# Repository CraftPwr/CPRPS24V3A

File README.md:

# **Craft Power Labs - Open Source Lab Equipment Initiative**  
### **Bench Top Power Supply - CPRPS24V3A**  
An open-source variable lab bench power supply designed for education, hobbyists, and non-profit initiatives. Part of the **Craft Power Labs Initiative**, funded initially by **DERBI / Nidhi Prayas**.  

---

## **📜 Project Overview**  
Craft Power Labs aims to provide accessible, high-quality, and open-source lab equipment for electronics learning and research. This power supply is built to match the essential features of commercial-grade bench power supplies while remaining completely open-source for personal, educational, and non-commercial use.  

---

## **📊 Technical Specifications (Datasheet)**  

| **Feature**             | **Specification**             |
|-------------------------|-----------------------------|
| **Input Supply**        | 110V ~ 220V AC              |
| **Variable Voltage**    | 0V to 24V                   |
| **Current Capacity**    | Up to 3A                    |
| **Voltage Resolution**  | 10mV                        |
| **Current Limit Resolution** | 50mA                 |
| **Voltmeter Resolution** | 100mV                      |
| **Ammeter Resolution**  | 100mA                        |
| **Noise & Ripple (@ 20MHz)** | < 50mV               |
| **Operating Modes**     | Constant Voltage (CV), Constant Current (CC) |
| **Safety Features**     | Over Current, Short Circuit, Reverse Voltage Bypass |
| **Display**            | 1-inch Volt-Amp Meter Digits |
| **Control**            | Multi-Turn Potentiometers    |
| **Connectors**         | 4mm Banana Sockets          |
| **AC Port**            | IEC 14 Port with Illuminated SPST Switch + Fuse |

---

## **📷 Images & Renders**  

---

## **📜 Licensing**  
This project is licensed under **CC BY-NC-SA 4.0**, which means:  
✔ Free to use, modify, and distribute for personal, educational, and non-commercial purposes.  
✔ Must provide attribution and share derivative works under the same license.  
❌ **Not for commercial use** without explicit permission.  

For more details, see: [LICENSE.md](./LICENSE.md)  

📩 **For inquiries, contact us:**  
**Email:** [connect@craftpower.cc](mailto:connect@craftpower.cc)  
**Website:** [https://craftpower.cc](https://craftpower.cc)  

---

## **🛠 Getting Started**  
### **1️⃣ Hardware Design**  
- Schematic and PCB files are available in the `/hardware` directory.  
- Designed using **KiCad**.  

### **2️⃣ Assembly & Testing**  
- Refer to the `assembly_guide.md` for step-by-step assembly instructions.  
- Use the `calibration_guide.md` to fine-tune voltage and current accuracy.  

---

## **🛠 Contributing**  
We welcome contributions! If you'd like to improve the design, add new features, or fix bugs:  
1. Fork this repository  
2. Create a new branch (`feature-new-component`)  
3. Submit a Pull Request  

---

## **🌍 Join the Community**  
Be part of our mission to make electronics lab equipment open-source and accessible.  

💬 **Join our discussion forum**: [Forum Link]  
📢 **Follow updates**: [Social Media Link]  

---

🚀 **Craft Power Labs - Powering Learning, One Bench at a Time!**

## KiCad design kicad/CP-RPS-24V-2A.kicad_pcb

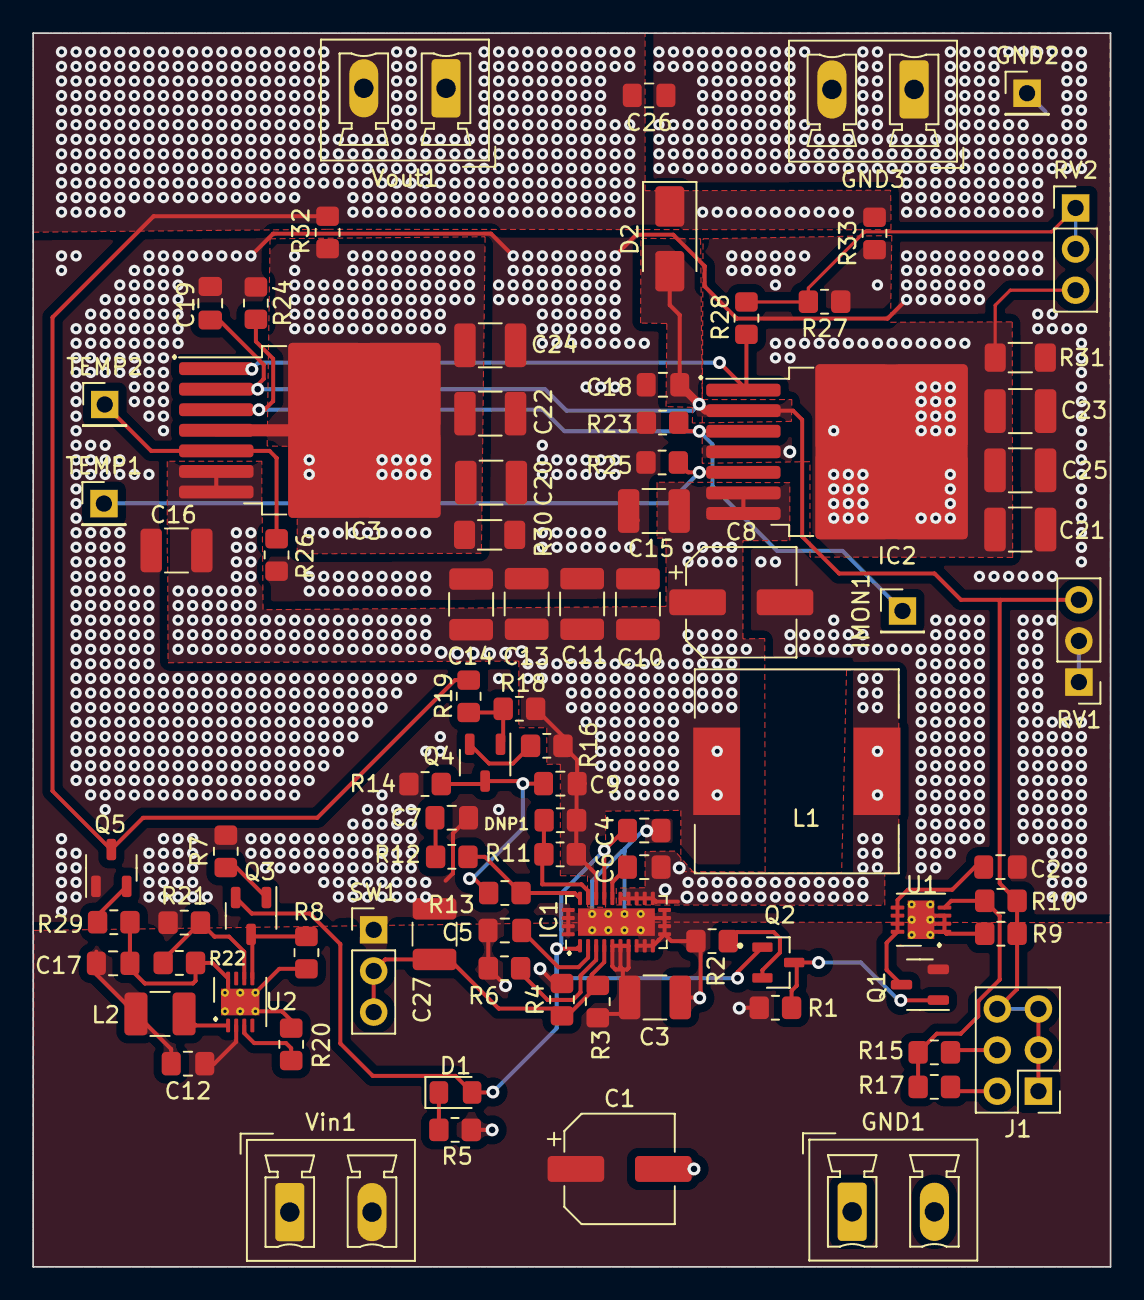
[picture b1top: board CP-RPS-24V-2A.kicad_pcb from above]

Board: 2 copper layers, 66.5 x 76.2 mm, 87 parts (0 on the bottom side), 39 nets.

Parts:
C1: 22uF; CP_Elec_6.3x7.7
C2, C4, C12, C26: 1uF; C_0805_2012Metric_Pad1.18x1.45mm_HandSolder
C3: 10uF 50V; C_1210_3225Metric_Pad1.33x2.70mm_HandSolder
C5, C6: 0.1uF; C_0805_2012Metric_Pad1.18x1.45mm_HandSolder
C7: (OPT); C_0805_2012Metric_Pad1.18x1.45mm_HandSolder
C8: 100uF; CP_Elec_6.3x7.7
C9: 1nF; C_0805_2012Metric_Pad1.18x1.45mm_HandSolder
C10: DNP; C_1210_3225Metric_Pad1.33x2.70mm_HandSolder
C11, C13, C14, C15, C16, C20, C21, C22, C23, C24, C25: 10uF; C_1210_3225Metric_Pad1.33x2.70mm_HandSolder
C17: 10uF; C_0805_2012Metric_Pad1.18x1.45mm_HandSolder
C18, C19: 0.01uF; C_0805_2012Metric_Pad1.18x1.45mm_HandSolder
C27: 39.6uF; C_1210_3225Metric_Pad1.33x2.70mm_HandSolder
D1: LED; LED_0805_2012Metric_Pad1.15x1.40mm_HandSolder
D2: B140; D_SMA
DNP1: 5.1K; R_0805_2012Metric_Pad1.20x1.40mm_HandSolder
GND1, GND3: PhoenixContact_MCV_1,5_2-G-5.08_1x02_P5.08mm_Vertical
GND2: TestPoint; PinHeader_1x01_P2.54mm_Vertical
IC1: LT8612EUDE#PBF; QFN-28-1EP_3x6mm_P0.5mm_EP1.7x4.75mm_ThermalVias
IC2, IC3: LT3081ER_PBF; TO-263-7_TabPin8
IMON1: 10V-40V; PinHeader_1x01_P2.54mm_Vertical
J1: Conn_02x03_Odd_Even; PinHeader_2x03_P2.54mm_Vertical
L1: 5.5uH; L_12x12mm_H4.5mm
L2: 470uH; L_1210_3225Metric_Pad1.42x2.65mm_HandSolder
Q1: SI2309CDS; SOT-23-3
Q2: CMST3904; SOT95P230X110-3N
Q3, Q4: MMBT3906; SOT-23-3
Q5: FMMT493; SOT-23-3
R1, R11: 5.1K; R_0805_2012Metric_Pad1.20x1.40mm_HandSolder
R2: 2.7K; R_0805_2012Metric_Pad1.20x1.40mm_HandSolder
R3: 499K; R_0805_2012Metric_Pad1.20x1.40mm_HandSolder
R4: 54.9K; R_0805_2012Metric_Pad1.20x1.40mm_HandSolder
R5, R29: 549E; R_0805_2012Metric_Pad1.20x1.40mm_HandSolder
R6: 60.4K; R_0805_2012Metric_Pad1.20x1.40mm_HandSolder
R7: 1K; R_0805_2012Metric_Pad1.20x1.40mm_HandSolder
R8, R25, R26: 10K; R_0805_2012Metric_Pad1.20x1.40mm_HandSolder
R9: 200E; R_0805_2012Metric_Pad1.20x1.40mm_HandSolder
R10: 47.5K; R_0805_2012Metric_Pad1.20x1.40mm_HandSolder
R12: (OPT); R_0805_2012Metric_Pad1.20x1.40mm_HandSolder
R13, R16, R23, R24: 1.00K; R_0805_2012Metric_Pad1.20x1.40mm_HandSolder
R14: 4.99K; R_0805_2012Metric_Pad1.20x1.40mm_HandSolder
R15: 73.2K; R_0805_2012Metric_Pad1.20x1.40mm_HandSolder
R17: 11.3K; R_0805_2012Metric_Pad1.20x1.40mm_HandSolder
R18, R19: 100K; R_0805_2012Metric_Pad1.20x1.40mm_HandSolder
R20: 806K; R_0805_2012Metric_Pad1.20x1.40mm_HandSolder
R21: 1.47M; R_0805_2012Metric_Pad1.20x1.40mm_HandSolder
R22: 280K; R_0805_2012Metric_Pad1.20x1.40mm_HandSolder
R27: 3.92K; R_0805_2012Metric_Pad1.20x1.40mm_HandSolder
R28: 100E; R_0805_2012Metric_Pad1.20x1.40mm_HandSolder
R30, R31: 10K; R_1206_3216Metric_Pad1.30x1.75mm_HandSolder
R32, R33: 0.01E; R_0805_2012Metric_Pad1.20x1.40mm_HandSolder
RV1: 10K; PinHeader_1x03_P2.54mm_Vertical
RV2: 5K; PinHeader_1x03_P2.54mm_Vertical
SW1: SW_SPDT_321; PinHeader_1x03_P2.54mm_Vertical
TEMP1: TestPoint; PinHeader_1x01_P2.54mm_Vertical
TEMP2: 10V-40V; PinHeader_1x01_P2.54mm_Vertical
U1: LT3092EDD; DFN-8-1EP_3x3mm_P0.5mm_EP1.65x2.38mm_ThermalVias
U2: LTC3632EDD; DFN-8-1EP_3x3mm_P0.5mm_EP1.65x2.38mm_ThermalVias
Vin1: 10V-40V; PhoenixContact_MCV_1,5_2-G-5.08_1x02_P5.08mm_Vertical
Vout1: 0V-24V; PhoenixContact_MCV_1,5_2-G-5.08_1x02_P5.08mm_Vertical

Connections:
/IC1_TEMP: IC2.5 (TEMP), R25.1, TEMP1.1
/IC2_FB: IC1.24 (FB), R12.1, R13.2
/IC3_TEMP: IC3.5 (TEMP), R26.1, TEMP2.1
/ILIM+: C21.2, C23.2, C25.2, IC2.4 (OUT), IC2.TAB (OUT), R27.1, R31.1, R33.2, RV2.3
/ILIM-: R27.2, R28.1, RV2.1, RV2.2
/IMON: IC2.3 (IMON), IC3.3 (IMON), IMON1.1, R23.2, R24.2
/INTVCC: C4.1, D1.2 (A), IC1.1 (SYNC), IC1.21 (INTVCC), Q2.1 (B), Q3.2 (E)
/SW: C6.1, IC1.15 (SW_1), IC1.16 (SW_2), IC1.17 (SW_3), IC1.18 (SW_4), IC1.19 (SW_5), L1.1
/U1_SET: R10.2, R15.2, R17.2, U1.4 (SET)
/U2_VFB: R21.2, R22.1, U2.6 (VFB)
/Vin: C1.1 (+), C3.1, C12.1, IC1.5 (VIN_1), IC1.6 (VIN_2), IC1.7 (VIN_3), Q1.2, R1.1, R3.1, U2.2 (VIN), Vin1.1, Vin1.2
GND: C1.2 (-), C2.2, C3.2, C4.2, C5.2, C7.1, C8.2 (-), C10.1, C11.1, C12.2, C13.1, C14.1, C15.1, C16.1, C17.2, C18.1, C19.1, C20.1, C21.1, C22.1, C23.1, C24.1, C25.1, C26.1, C27.2, GND1.1, GND1.2, GND2.1, GND3.1, GND3.2, IC1.8 (PGND_1), IC1.9 (PGND_2), IC1.10 (PGND_3), IC1.11 (GND_1), IC1.12 (GND_2), IC1.13 (GND_3), IC1.14 (GND_4), IC1.25 (GND_5), IC1.26 (GND_6), IC1.27 (GND_7), IC1.28 (GND_8), IC1.29 (GND_9), L2.2, Q5.1 (B), R2.2, R4.2, R5.2, R6.2, R7.2, R14.2, R21.1, R23.1, R24.1, R25.2, R26.2, R30.2, R31.2, RV1.1, RV1.2, SW1.1 (C)
unnamed: C7.2, R12.2
unnamed: C8.1 (+), C9.1, C10.2, C11.2, C13.2, C14.2, C15.2, C16.2, DNP1.1, IC1.22 (BIAS), IC2.6 (IN), IC2.7 (IN), IC3.6 (IN), IC3.7 (IN), L1.2, R11.1, R16.1, R18.1
unnamed: C20.2, C22.2, C24.2, IC3.4 (OUT), IC3.TAB (OUT), R30.1, R32.2
unnamed: D1.1 (K), R5.1
unnamed: C18.2, C19.2, D2.2 (A), IC2.2 (SET), IC3.2 (SET), J1.1, J1.3, J1.5, J1.6, R9.1, R10.1, RV1.3
unnamed: C26.2, D2.1 (K), Q5.3 (C), R19.2, R32.1, R33.1, Vout1.1, Vout1.2
unnamed: C6.2, IC1.20 (BST)
unnamed: C27.1, IC1.4 (EN/UV), R3.2, R4.1, SW1.2 (B), SW1.3 (A)
unnamed: DNP1.2, IC1.23 (PG), R11.2
unnamed: IC1.3 (RT), R6.1
unnamed: C5.1, IC1.2 (TR/SS)
unnamed: IC2.1 (ILIM), IC3.1 (ILIM), R28.2
unnamed: J1.2, R17.1
unnamed: J1.4, R15.1
unnamed: Q1.1, Q2.3 (C), R1.2
unnamed: Q2.2 (E), R2.1
unnamed: Q3.1 (B), R7.1
unnamed: Q3.3 (C), R8.1, U2.5 (RUN)
unnamed: Q4.1 (B), R18.2, R19.1
unnamed: C9.2, Q4.3 (C), R13.1, R14.1
unnamed: Q4.2 (E), R16.2
unnamed: Q5.2 (E), R29.1
unnamed: R9.2, U1.1 (OUT_2), U1.2 (OUT), U1.3 (NC_2), U1.9 (EPAD)
unnamed: C2.1, Q1.3, U1.5 (NC_3), U1.6 (NC), U1.7 (IN_2), U1.8 (IN)
unnamed: C17.1, R8.2, R20.2, R22.2, R29.2, U2.8 (GND), U2.9 (EPAD)
unnamed: R20.1, U2.3 (ISET)
unnamed: L2.1, U2.1 (SW)

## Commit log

2025-03-19 stress test
